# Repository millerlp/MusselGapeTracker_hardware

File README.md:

# MusselGapeTracker_hardware
 Mussel Gape Tracker circuit board designs

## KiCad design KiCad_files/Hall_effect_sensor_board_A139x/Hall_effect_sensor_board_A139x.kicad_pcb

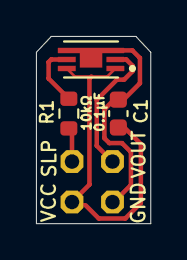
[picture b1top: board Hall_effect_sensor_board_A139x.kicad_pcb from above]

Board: 2 copper layers, 6.4 x 10.4 mm, 4 parts (0 on the bottom side), 5 nets.

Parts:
C1: 0.1µF; C_0603_1608Metric
HALL1_HEADER1: PINHD-2X21.5MM_SILK; 2X2_2.25MM
R1: 10kΩ; R_0603_1608Metric
U1: A1395SEHLT-T; SENSOR_A1395SEHLT-T

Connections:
/HALL1_GND: C1.2, HALL1_HEADER1.P$1 (1), U1.3 (GND), U1.4 (GND)
/HALL1_VCC: C1.1, HALL1_HEADER1.P$2 (2), U1.1 (VCC), U1.6 (VREF)
/HALL1_VOUT: HALL1_HEADER1.P$3 (3), U1.2 (OUT)
/HALL1_~SLEEP_IN: HALL1_HEADER1.P$4 (4), R1.1
/~SLEEP1: R1.2, U1.5 (~SLEEP)

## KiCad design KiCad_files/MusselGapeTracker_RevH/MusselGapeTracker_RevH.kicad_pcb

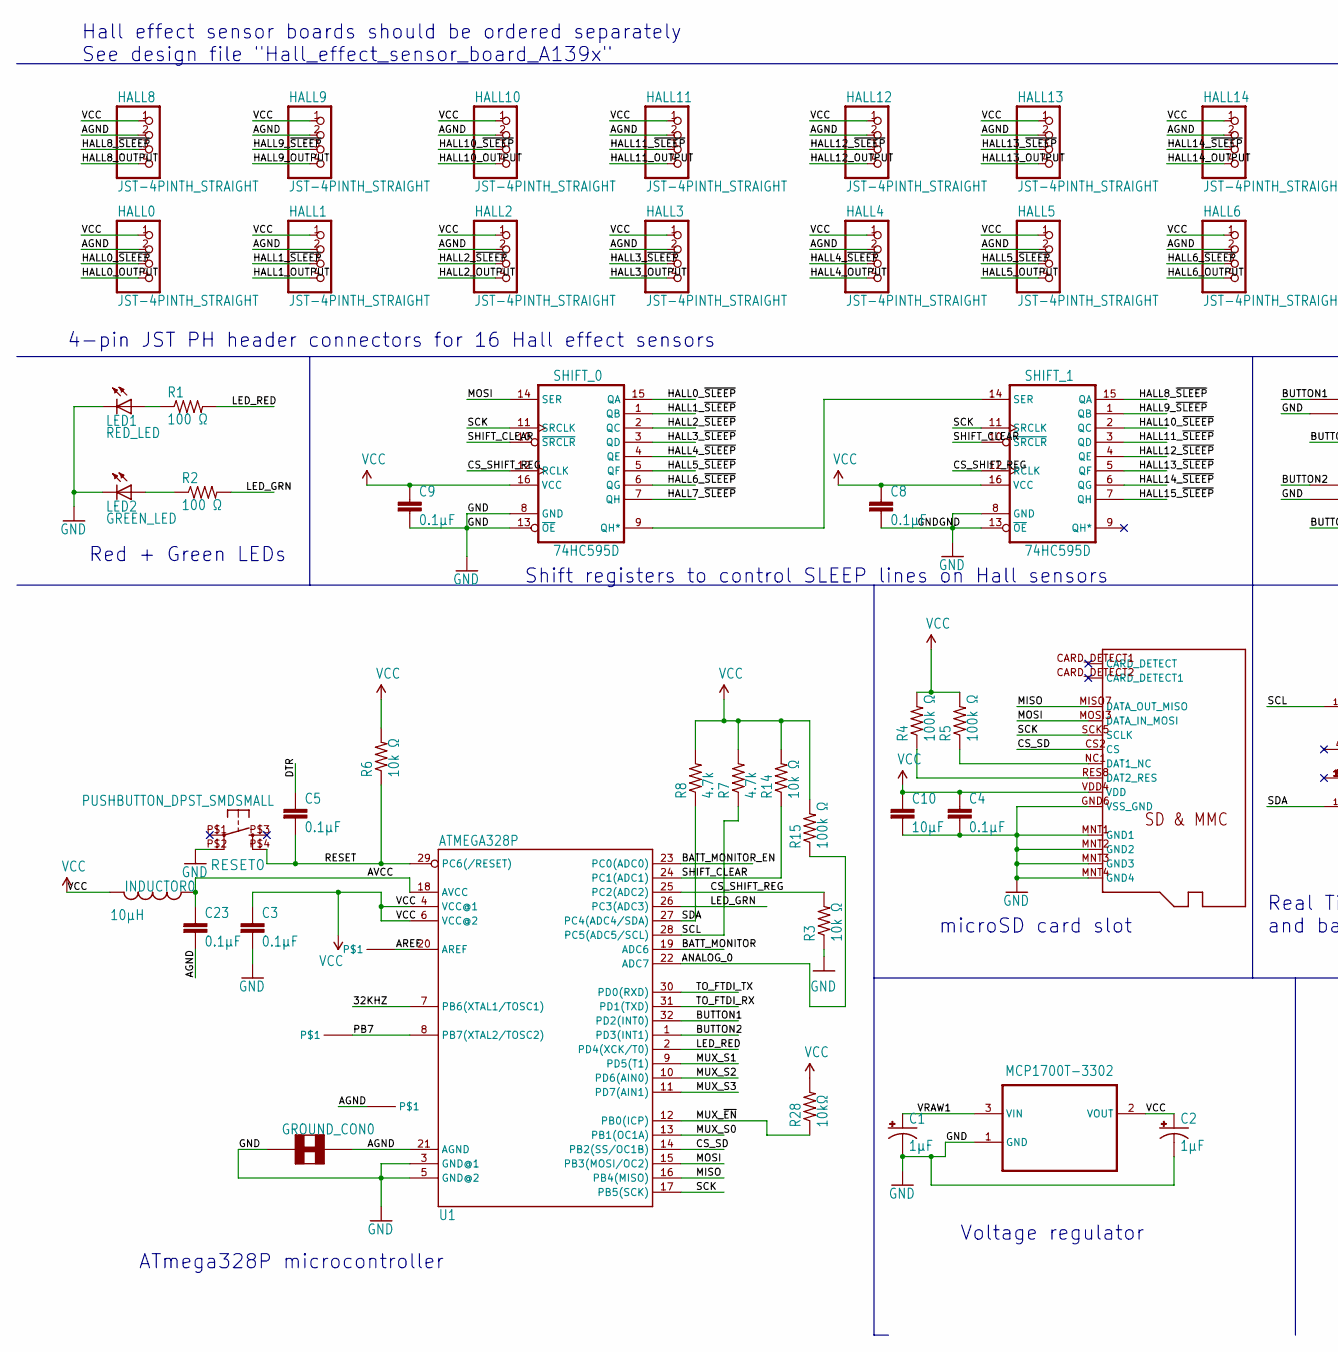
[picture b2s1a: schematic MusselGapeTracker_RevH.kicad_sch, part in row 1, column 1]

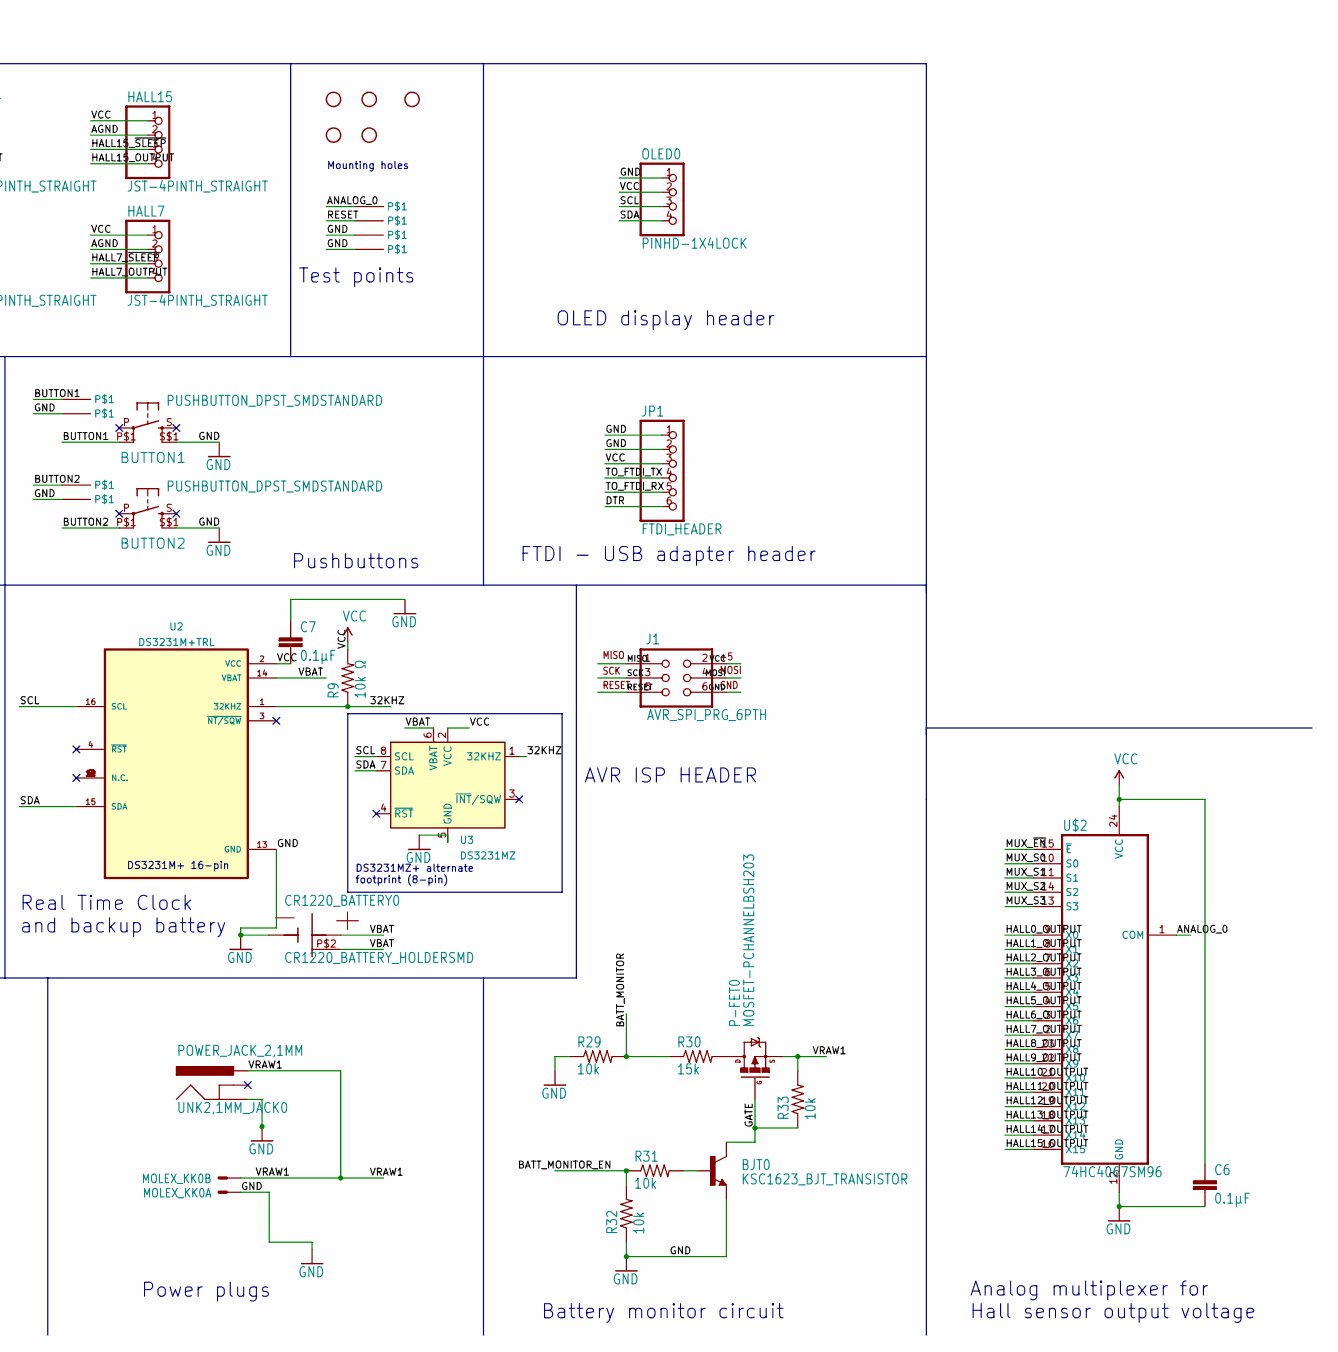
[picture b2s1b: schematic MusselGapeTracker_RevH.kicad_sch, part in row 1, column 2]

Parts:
BJT0: KSC1623_BJT_TRANSISTOR; SOT23
BUTTON1, BUTTON2: PUSHBUTTON_DPST_SMDSTANDARD; PUSHBUTTON_DPST_SMD
C1, C2: 1µF; PANASONIC_B
C3, C4, C5, C6, C7, C8, C9, C23: 0.1µF; R_0603_1608Metric_Pad0.98x0.95mm_HandSolder
C10: 10µF; R_0603_1608Metric_Pad0.98x0.95mm_HandSolder
CR1220_BATTERY0: CR1220_BATTERY_HOLDERSMD; CR1220_BATTERY_HOLDER_SMD
GND0: PINHD-1X1SMALL; 1X01_SMALL
GROUND_CON0: SOLDER_JUMPER_TRACESTANDARD; SJ_2S-TRACE
HALL0, HALL1, HALL2, HALL3, HALL4, HALL5, HALL6, HALL7, HALL8, HALL9, HALL10, HALL11, HALL12, HALL13, HALL14, HALL15: JST-4PINTH_STRAIGHT; JST-PH-4-THM
INDUCTOR0: 10µH; I_0805
J1: AVR_SPI_PRG_6PTH; 2X3
JP1: FTDI_HEADER; 1X06-RIGHT_ANGLE
LED1: RED_LED; CHIPLED_0805
LED2: GREEN_LED; CHIPLED_0805
MCP1700T-3302: MCP1700T-3302E/TT; SOT95P237X112-3N
MOLEX_KK0: 22-23-2021
OLED0: PINHD-1X4LOCK; 1X04_LOCK
P-FET0: MOSFET-PCHANNELBSH203; SOT23-3
PB7: PINHD-1X1SMALL; 1X01_SMALL
R1, R2: 100 Ω; R_0603_1608Metric_Pad0.98x0.95mm_HandSolder
R3, R6, R9, R14: 10k Ω; R_0603_1608Metric_Pad0.98x0.95mm_HandSolder
R4, R5, R15: 100k Ω; R_0603_1608Metric_Pad0.98x0.95mm_HandSolder
R7, R8: 4.7k; R_0603_1608Metric_Pad0.98x0.95mm_HandSolder
R28: 10kΩ; R_0603_1608Metric_Pad0.98x0.95mm_HandSolder
R29, R31, R32, R33: 10k; R_0603_1608Metric_Pad0.98x0.95mm_HandSolder
R30: 15k; R_0603_1608Metric_Pad0.98x0.95mm_HandSolder
RESET0: PUSHBUTTON_DPST_SMDSMALL; PUSHBUTTON_SPST_PTS525_SERIES
SHIFT_0, SHIFT_1: 74HC595D; SO16
STANDOFF1, STANDOFF2, STANDOFF3: STAND-OFF4-40; STAND-OFF
STANDOFF4_M2, STANDOFF5_M2: STAND-OFFM2; STAND-OFF_M2
U1: ATMEGA328P; TQFP32-08
U2: DS3231M+TRL; SOIC127P1032X265-16N
U3: DS3231MZ; SOIC-8_3.9x4.9mm_P1.27mm
U$1: MICROSD_MOLEX_REVERSECURRENT; MICROSD_SOCKET_MOLEX_REVERSEMOUNT
U$2: 74HC4067SM96; SSOP24
U$3, U$4, U$6, U$7, U$8, U$9, U$10, U$11, U$17: PINHD-1X1SMALL; 1X01_SMALL
UNK2,1MM_JACK0: POWER_JACK_2,1MM; POWER_JACK_DC_2,1MM

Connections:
/32KHZ: R9.1, U1.7 (PB6(XTAL1/TOSC1)), U2.1 (32KHZ), U3.1 (32KHZ)
/AGND: C23.2, GROUND_CON0.2, HALL0.2, HALL1.2, HALL2.2, HALL3.2, HALL4.2, HALL5.2, HALL6.2, HALL7.2, HALL8.2, HALL9.2, HALL10.2, HALL11.2, HALL12.2, HALL13.2, HALL14.2, HALL15.2, U1.21 (AGND), U$11.1
/ANALOG_0: R15.1, U1.22 (ADC7), U$2.1 (COM), U$10.1
/AREF: U1.20 (AREF), U$17.1
/AVCC: C23.1, INDUCTOR0.P$1 (1), U1.18 (AVCC)
/BATT_MONITOR: R29.2, R30.1, U1.19 (ADC6)
/BATT_MONITOR_EN: R31.1, R32.2, U1.23 (PC0(ADC0))
/BUTTON1: BUTTON1.P$1 (P1), U1.32 (PD2(INT0)), U$6.1
/BUTTON2: BUTTON2.P$1 (P1), U1.1 (PD3(INT1)), U$8.1
/CS_SD: U1.14 (PB2(SS/OC1B)), U$1.CS2 (CS)
/CS_SHIFT_REG: R3.2, SHIFT_0.12 (RCLK), SHIFT_1.12 (RCLK), U1.25 (PC2(ADC2))
/DTR: C5.1, JP1.6
/GATE: BJT0.3 (C), P-FET0.1 (G), R33.1
/HALL0_OUTPUT: HALL0.4, U$2.9 (X0)
/HALL0_~SLEEP: HALL0.3, SHIFT_0.15 (QA)
/HALL1_OUTPUT: HALL1.4, U$2.8 (X1)
/HALL1_~SLEEP: HALL1.3, SHIFT_0.1 (QB)
/HALL2_OUTPUT: HALL2.4, U$2.7 (X2)
/HALL2_~SLEEP: HALL2.3, SHIFT_0.2 (QC)
/HALL3_OUTPUT: HALL3.4, U$2.6 (X3)
/HALL3_~SLEEP: HALL3.3, SHIFT_0.3 (QD)
/HALL4_OUTPUT: HALL4.4, U$2.5 (X4)
/HALL4_~SLEEP: HALL4.3, SHIFT_0.4 (QE)
/HALL5_OUTPUT: HALL5.4, U$2.4 (X5)
/HALL5_~SLEEP: HALL5.3, SHIFT_0.5 (QF)
/HALL6_OUTPUT: HALL6.4, U$2.3 (X6)
/HALL6_~SLEEP: HALL6.3, SHIFT_0.6 (QG)
/HALL7_OUTPUT: HALL7.4, U$2.2 (X7)
/HALL7_~SLEEP: HALL7.3, SHIFT_0.7 (QH)
/HALL8_OUTPUT: HALL8.4, U$2.23 (X8)
/HALL8_~SLEEP: HALL8.3, SHIFT_1.15 (QA)
/HALL9_OUTPUT: HALL9.4, U$2.22 (X9)
/HALL9_~SLEEP: HALL9.3, SHIFT_1.1 (QB)
/HALL10_OUTPUT: HALL10.4, U$2.21 (X10)
/HALL10_~SLEEP: HALL10.3, SHIFT_1.2 (QC)
/HALL11_OUTPUT: HALL11.4, U$2.20 (X11)
/HALL11_~SLEEP: HALL11.3, SHIFT_1.3 (QD)
/HALL12_OUTPUT: HALL12.4, U$2.19 (X12)
/HALL12_~SLEEP: HALL12.3, SHIFT_1.4 (QE)
/HALL13_OUTPUT: HALL13.4, U$2.18 (X13)
/HALL13_~SLEEP: HALL13.3, SHIFT_1.5 (QF)
/HALL14_OUTPUT: HALL14.4, U$2.17 (X14)
/HALL14_~SLEEP: HALL14.3, SHIFT_1.6 (QG)
/HALL15_OUTPUT: HALL15.4, U$2.16 (X15)
/HALL15_~SLEEP: HALL15.3, SHIFT_1.7 (QH)
/LED_GRN: R2.2, U1.26 (PC3(ADC3))
/LED_RED: R1.2, U1.2 (PD4(XCK/T0))
/MISO: J1.1, U1.16 (PB4(MISO)), U$1.MISO7 (DATA_OUT_MISO)
/MOSI: J1.4, SHIFT_0.14 (SER), U1.15 (PB3(MOSI/OC2)), U$1.MOSI3 (DATA_IN_MOSI)
/MUX_S0: U1.13 (PB1(OC1A)), U$2.10 (S0)
/MUX_S1: U1.9 (PD5(T1)), U$2.11 (S1)
/MUX_S2: U1.10 (PD6(AIN0)), U$2.14 (S2)
/MUX_S3: U1.11 (PD7(AIN1)), U$2.13 (S3)
/MUX_~EN: R28.1, U1.12 (PB0(ICP)), U$2.15 (~E)
/PB7: PB7.1, U1.8 (PB7(XTAL2/TOSC2))
/RESET: C5.2, J1.5, R6.1, RESET0.P$4 (S1), U1.29 (PC6(/RESET)), U$3.1
/SCK: J1.3, SHIFT_0.11 (SRCLK), SHIFT_1.11 (SRCLK), U1.17 (PB5(SCK)), U$1.SCK5 (SCLK)
/SCL: OLED0.3, R7.1, U1.28 (PC5(ADC5/SCL)), U2.16 (SCL), U3.8 (SCL); also elsewhere on the board
/SDA: OLED0.4, R8.1, U1.27 (PC4(ADC4/SDA)), U2.15 (SDA), U3.7 (SDA); also elsewhere on the board
/SHIFT_CLEAR: R14.1, SHIFT_0.10 (~SRCLR), SHIFT_1.10 (~SRCLR), U1.24 (PC1(ADC1))
/TO_FTDI_RX: JP1.5, U1.31 (PD1(TXD))
/TO_FTDI_TX: JP1.4, U1.30 (PD0(RXD))
/VBAT: CR1220_BATTERY0.P$1 (VBAT), CR1220_BATTERY0.P$2, U2.14 (VBAT), U3.6 (VBAT)
/VRAW1: C1.+, MCP1700T-3302.3 (VIN), MOLEX_KK0.2 (S), P-FET0.2 (S), R33.2, UNK2,1MM_JACK0.P$1 (PWR)
GND: BJT0.2 (E), BUTTON1.S$1 (S1), BUTTON2.S$1 (S1), C1.-, C2.-, C3.2, C4.2, C6.2, C7.1, C8.2, C9.2, C10.2, CR1220_BATTERY0.GND, GND0.1, GROUND_CON0.1, J1.6, JP1.1, JP1.2, LED1.C, LED2.C, MCP1700T-3302.1 (GND), MOLEX_KK0.1 (S), OLED0.1, R3.1, R29.1, R32.1, RESET0.P$2 (P1), SHIFT_0.8 (GND), SHIFT_0.13 (~OE), SHIFT_1.8 (GND), SHIFT_1.13 (~OE), U1.3 (GND@1), U1.5 (GND@2), U2.13 (GND), U3.5 (GND), U$1.GND6 (VSS_GND), U$1.MNT1 (GND1), U$1.MNT2 (GND2), U$1.MNT3 (GND3), U$1.MNT4 (GND4), U$2.12 (GND), U$4.1, U$7.1, U$9.1, UNK2,1MM_JACK0.P$2 (GND); also elsewhere on the board
unnamed: BJT0.1 (B), R31.2
unnamed: LED1.A, R1.1
unnamed: LED2.A, R2.1
unnamed: P-FET0.3 (D), R30.2
unnamed: SHIFT_0.9 (QH*), SHIFT_1.14 (SER)
unnamed: R5.1, U$1.NC1 (DAT1_NC)
unnamed: R4.1, U$1.RES8 (DAT2_RES)
VCC: C2.+, C3.1, C4.1, C6.1, C7.2, C8.1, C9.1, C10.1, HALL0.1, HALL1.1, HALL2.1, HALL3.1, HALL4.1, HALL5.1, HALL6.1, HALL7.1, HALL8.1, HALL9.1, HALL10.1, HALL11.1, HALL12.1, HALL13.1, HALL14.1, HALL15.1, INDUCTOR0.P$2 (2), J1.2, JP1.3, MCP1700T-3302.2 (VOUT), OLED0.2, R4.2, R5.2, R6.2, R7.2, R8.2, R9.2, R14.2, R15.2, R28.2, SHIFT_0.16 (VCC), SHIFT_1.16 (VCC), U1.4 (VCC@1), U1.6 (VCC@2), U2.2 (VCC), U3.2 (VCC), U$1.VDD4 (VDD), U$2.24 (VCC); also elsewhere on the board

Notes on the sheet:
Voltage regulator
OLED display header
DS3231M+ 16-pin
microSD card slot
Real Time Clock and backup battery
Battery monitor circuit
4-pin JST PH header connectors for 16 Hall effect sensors
Hall effect sensor boards should be ordered separately See design file "Hall_effect_sensor_board_A139x"
Pushbuttons
Test points
ATmega328P microcontroller
FTDI - USB adapter header
Analog multiplexer for Hall sensor output voltage
Power plugs
Mounting holes
Shift registers to control SLEEP lines on Hall sensors
DS3231MZ+ alternate footprint (8-pin)
AVR ISP HEADER
Red + Green LEDs

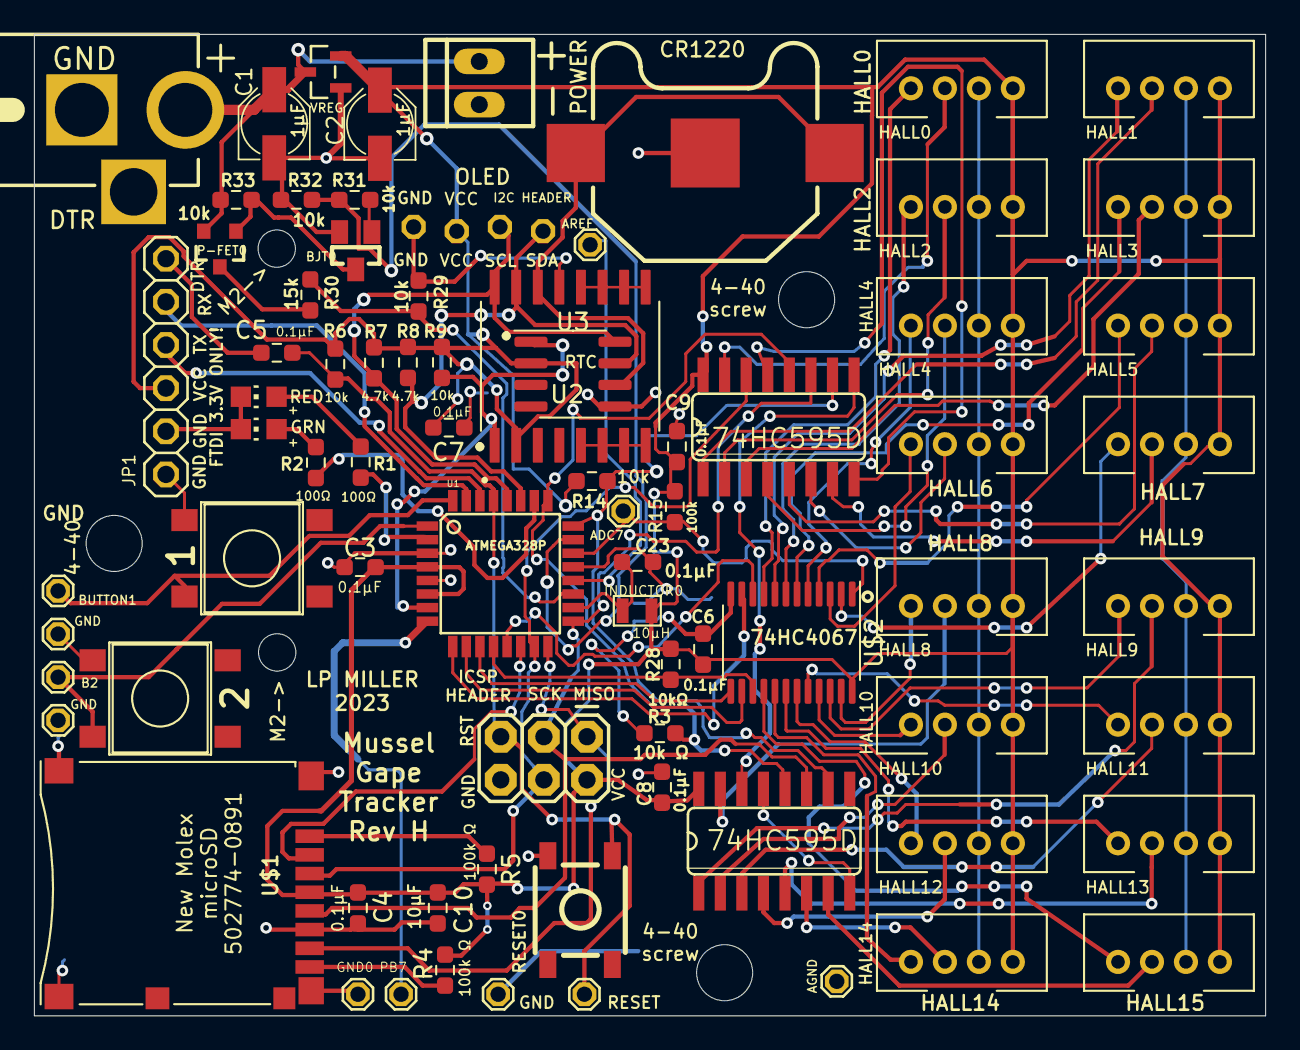
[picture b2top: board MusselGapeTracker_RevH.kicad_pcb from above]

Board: 2 copper layers, 72.5 x 57.8 mm, 83 parts (1 on the bottom side), 73 nets.

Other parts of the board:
OLED: PINHD-1X4LOCK; 1X04_LOCK

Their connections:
/SCL: OLED.3; also elsewhere on the board
/SDA: OLED.4; also elsewhere on the board
GND: OLED.1; also elsewhere on the board
VCC: OLED.2; also elsewhere on the board

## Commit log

2023-12-08 Update the ignore file
2023-12-08 BOMs
2023-12-08 Catching these up
2025-03-18 Parts list Excel files
